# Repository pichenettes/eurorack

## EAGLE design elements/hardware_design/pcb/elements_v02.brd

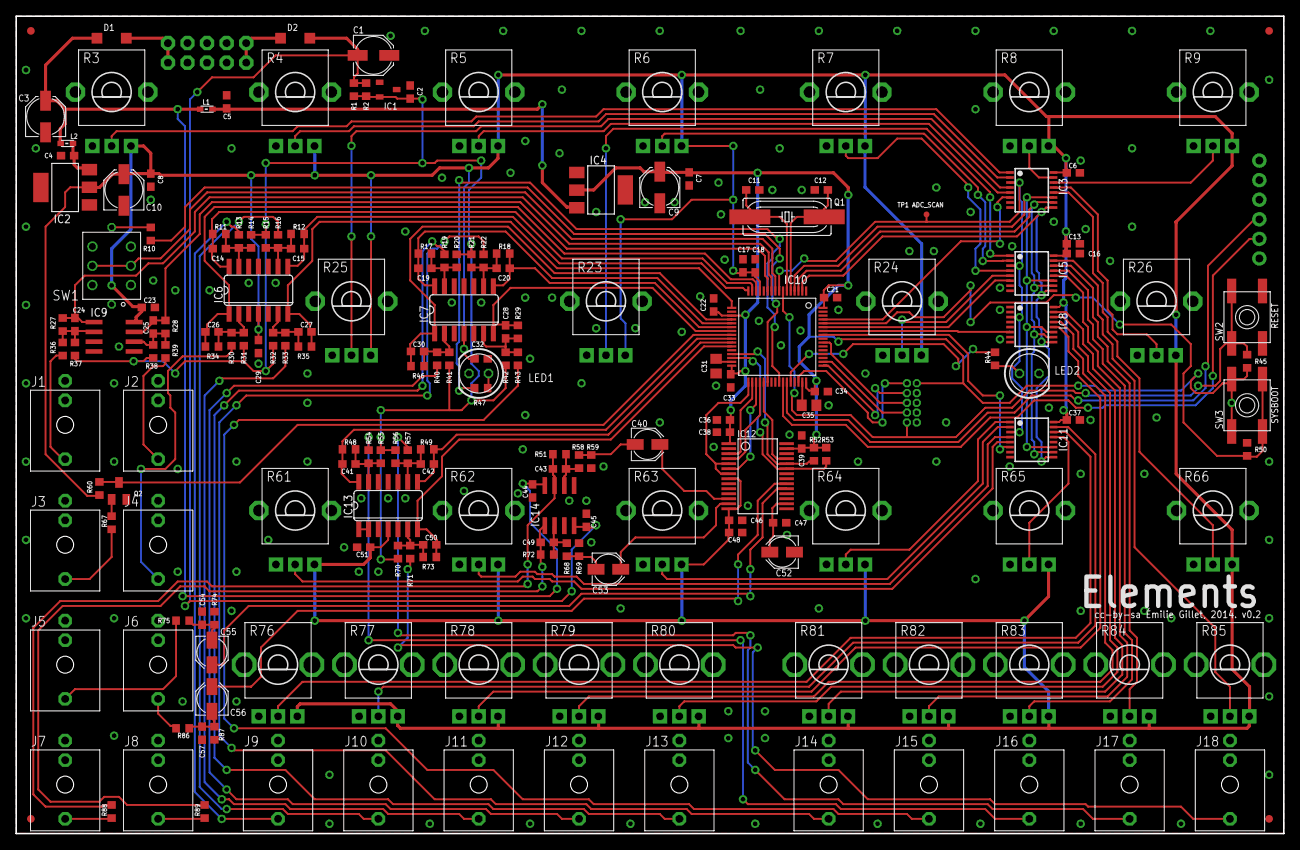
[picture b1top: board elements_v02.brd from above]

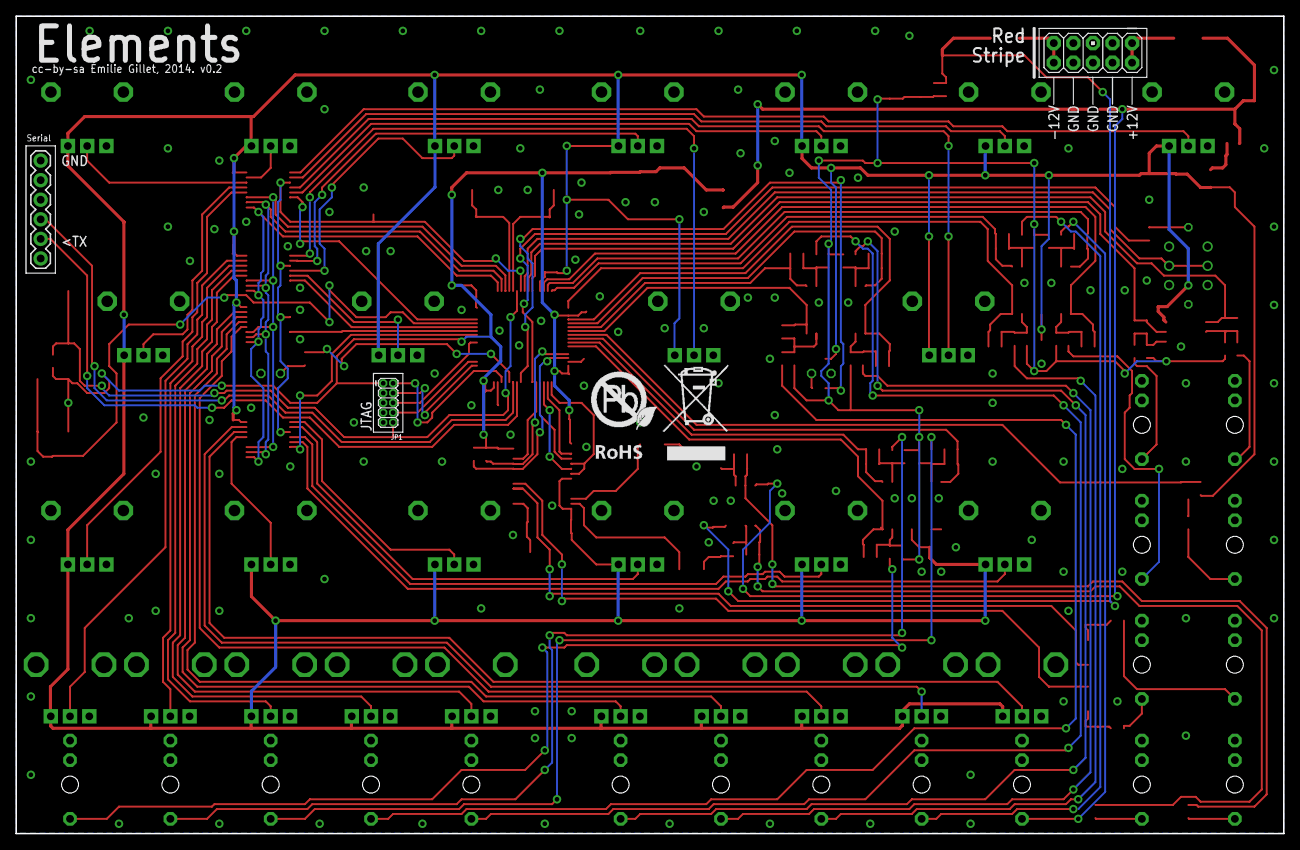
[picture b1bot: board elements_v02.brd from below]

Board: 2 copper layers, 164.5 x 106.0 mm, 198 parts (4 on the bottom side), 131 nets.

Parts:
C1, C3, C9, C10: 22u; PANASONIC_C
C2, C4, C5, C6, C7, C8, C13, C16, C18, C21, C22, C23, C29, C32, C33, C34, C37, C38, C39, C44, C45, C46, C47, C51: 100n; C0603
C11, C12, C43, C49: 18p; C0603
C14, C15, C19, C20, C24, C25, C26, C27, C28, C30, C41, C42, C50: 3.3n; C0603
C17, C36, C48: 1u; C0603
C31, C35: 2.2u; C0805
C40, C52, C53, C55, C56: 10u; PANASONIC_B
C54, C57: 220p; C0603
D1, D2: 1N5819HW; SOD123
F1, F2, F3, F4: FIDUCIAL1X2; FIDUCIAL-1X2
IC1: LM4040B10; DBZ_R-PDSO-G3
IC2, IC4: LM1117-3.3; SOT223
IC3, IC5, IC8, IC11: 4051PW; TSSOP16
IC6, IC7, IC13: MCP6004; SO14
IC9: MCP6002; SO08
IC10: STM32F405RGT6; TQFP-10X10-64
IC12: WM8731; SSOP28
IC14: LME49720; SO08
J1, J2, J3, J4, J5, J6, J7, J8, J9, J10, J11, J12, J13, J14, J15, J16, J17, J18: PJ301_THONKICONN6; WQP_PJ_301M6
JP1: M05X2MINIJTAG; 2X5-1.27
JP2: 1X06
JP3: M05X2PTH; AVR_ICSP
L1, L2: 0603
LED1: SSL-LX5093TC; LED5MM
LED2: SSL-LX5093PC; LED5MM
Q1: 8MHz; HC49UP
Q2: MMBT3904; SOT23-BEC
R1, R2, R88, R89: 1.0k; R0603
R3, R4, R5, R6, R7, R8, R9, R23, R24, R25, R26, R61, R62, R63, R64, R65, R66: 10kB; ALPS_POT_VERTICAL_PS
R10: 33; R0603
R11, R12, R17, R18, R28, R29, R35, R46, R48, R49, R73: 20k; R0603
R13, R16, R19, R22, R30, R33, R36, R39, R40, R43, R54, R57, R67, R71: 100k; R0603
R14, R15, R20, R21, R32, R38, R41, R42, R55, R56, R70: 120k; R0603
R27, R51, R59, R69, R72: 47k; R0603
R31: 200k; R0603
R34: 33k; R0603
R37: 180k; R0603
R44, R47, R52, R53: 2.2k; R0603
R45, R50, R60: 10k; R0603
R58, R68, R74, R87: 6.8k; R0603
R75, R86: 36k; R0603
R76, R77, R78, R79, R80, R81, R82, R83, R84, R85: 10kB; ALPS_POT_VERTICAL
SW1: LP4OA1PBCT
SW2, SW3: EVQ-Q2
TP1: ADC_TEST; PAD.03X.03
U$2: ROHS_BIG

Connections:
+3V3: C7.1, C9.+, C21.1, C22.1, C33.1, C34.1, C36.1, C38.1, C39.1, IC4.2, IC10.19, IC10.32, IC10.48, IC10.64, IC12.1, IC12.27, JP1.1, R45.2, R52.2, R53.2, SW3.B, SW3.B'
+3V3_A: C6.1, C8.1, C10.+, C13.1, C16.1, C17.1, C18.1, C23.1, C29.1, C32.1, C37.1, C46.1, C48.1, C51.1, IC2.2, IC3.16, IC5.16, IC6.4, IC7.4, IC8.16, IC9.8, IC10.13, IC11.16, IC12.8, IC12.14, IC13.4, R3.P$1, R4.P$1, R5.P$1, R6.P$1, R7.P$1, R8.P$1, R9.P$1, R23.P$1, R24.P$1, R25.P$1, R26.P$1, R60.2, R61.P$1, R62.P$1, R63.P$1, R64.P$1, R65.P$1, R66.P$1, R76.P$1, R77.P$1, R78.P$1, R79.P$1, R80.P$1, R81.P$1, R82.P$1, R83.P$1, R84.P$1, R85.P$1
ADC_ADDR_0: IC3.11, IC5.11, IC8.11, IC10.4, IC11.11
ADC_ADDR_1: IC3.10, IC5.10, IC8.10, IC10.3, IC11.10
ADC_ADDR_2: IC3.9, IC5.9, IC8.9, IC10.2, IC11.9
ADC_BANK_0: IC10.57, IC11.6
ADC_BANK_1: IC8.6, IC10.58
ADC_BANK_2: IC5.6, IC10.59
ADC_BANK_3: IC3.6, IC10.61
ADC_BLOW_SHAPE: C15.2, IC6.8, IC10.16, R12.1
ADC_BLOW_TIMBRE: C27.2, IC6.7, IC10.17, R35.1
ADC_BOW_TIMBRE: C14.2, IC6.14, IC10.15, R11.1
ADC_BRIGHTNESS: C42.2, IC10.26, IC13.8, R49.1
ADC_DAMPING: C20.2, IC7.8, IC10.22, R18.1
ADC_FM: C25.2, IC9.7, IC10.11, R28.1
ADC_GEOMETRY: C28.2, IC7.7, IC10.23, R29.1
ADC_POSITION: C41.2, IC10.25, IC13.14, R48.1
ADC_POTS: IC3.3, IC5.3, IC8.3, IC10.8, IC11.3, TP1.P$1
ADC_PRESSURE: C26.2, IC6.1, IC10.14, R34.1
ADC_SPACE: C50.2, IC10.27, IC13.7, R73.1
ADC_STRIKE_SHAPE: C30.2, IC7.1, IC10.20, R46.1
ADC_STRIKE_TIMBRE: C19.2, IC7.14, IC10.21, R17.1
ADC_V_OCT: C24.2, IC9.1, IC10.10, R27.1
AREF_-10: C2.1, IC1.2, R1.2, R2.2, R14.2, R15.2, R20.2, R21.2, R31.2, R32.2, R37.2, R38.2, R41.2, R42.2, R55.2, R56.2, R70.2
BOOT_FLASH: IC10.60, R50.2, SW3.A, SW3.A'
GATE: IC10.24, Q2.C, R60.1
GND: C1.+, C2.2, C3.-, C4.2, C5.2, C6.2, C7.2, C8.2, C9.-, C10.-, C11.1, C12.1, C13.2, C16.2, C17.2, C18.2, C21.2, C22.2, C23.2, C29.2, C31.2, C32.2, C33.2, C34.2, C35.2, C36.2, C37.2, C38.2, C39.2, C44.2, C45.1, C46.2, C47.2, C48.2, C51.2, C52.-, C54.2, C57.2, IC1.1, IC2.1, IC3.7, IC3.8, IC4.1, IC5.7, IC5.8, IC6.3, IC6.5, IC6.10, IC6.11, IC6.12, IC7.3, IC7.5, IC7.10, IC7.11, IC7.12, IC8.1, IC8.2, IC8.4, IC8.5, IC8.7, IC8.8, IC9.3, IC9.4, IC9.5, IC10.12, IC10.18, IC10.28, IC10.63, IC11.7, IC11.8, IC11.12, IC12.11, IC12.15, IC12.21, IC12.22, IC12.28, IC13.3, IC13.5, IC13.10, IC13.11, IC13.12, IC14.3, IC14.5, J1.P1, J2.P1, J3.P1, J3.P2, J4.P1, J5.P1, J6.P1, J7.P1, J8.P1, J9.P1, J10.P1, J11.P1, J12.P1, J13.P1, J14.P1, J15.P1, J16.P1, J17.P1, J18.P1, JP1.3, JP1.5, JP1.9, JP2.1, JP3.3, JP3.4, JP3.5, JP3.6, JP3.7, JP3.8, LED1.K, LED2.K, Q2.E, R3.P$3, R4.P$3, R5.P$3, R6.P$3, R7.P$3, R8.P$3, R9.P$3, R23.P$3, R24.P$3, R25.P$3, R26.P$3, R50.1, R59.1, R61.P$3, R62.P$3, R63.P$3, R64.P$3, R65.P$3, R66.P$3, R69.1, R74.1, R76.P$3, R77.P$3, R78.P$3, R79.P$3, R80.P$3, R81.P$3, R82.P$3, R83.P$3, R84.P$3, R85.P$3, R87.1, SW1.L2, SW1.P3, SW1.P6, SW2.A, SW2.A'
I2C_SCL: IC10.29, IC12.24, R52.1
I2C_SDA: IC10.30, IC12.23, R53.1
I2S_LRCK: IC10.33, IC12.5, IC12.7
I2S_MCK: IC10.37, IC12.25
I2S_SCK: IC10.34, IC12.3
I2S_SIN: IC10.35, IC12.6
I2S_SOUT: IC10.36, IC12.4
JTCK: IC10.49, JP1.4
JTDI: IC10.50, JP1.8
JTDO: IC10.55, JP1.6
JTMS: IC10.46, JP1.2
LED_GATE: IC10.38, R10.1
LIN: C56.+, IC12.20
LOUT: C40.+, IC12.12
LOUT_JACK: J8.P3, R89.1
unnamed: J10.P3, R16.2
unnamed: C15.1, IC6.9, R12.2, R15.1, R16.1
unnamed: J13.P3, R19.2
unnamed: J9.P3, R13.2
unnamed: C14.1, IC6.13, R11.2, R13.1, R14.1
unnamed: J2.P3, R39.2
unnamed: C12.2, IC10.5, Q1.2
unnamed: C11.2, IC10.6, Q1.1
unnamed: C19.1, IC7.13, R17.2, R19.1, R20.1
unnamed: J1.P3, R36.2
unnamed: C24.1, IC9.2, R27.2, R36.1, R37.1
unnamed: J14.P3, R22.2
unnamed: C35.1, IC10.47
unnamed: C20.1, IC7.9, R18.2, R21.1, R22.1
unnamed: C25.1, IC9.6, R28.2, R38.1, R39.1
unnamed: J12.P3, R40.2
unnamed: C47.1, C52.+, IC12.16
unnamed: C56.-, C57.1, R86.1, R87.2
unnamed: C31.1, IC10.31
unnamed: J5.P3, R75.2
unnamed: J6.P3, R86.2
unnamed: C54.1, C55.-, R74.2, R75.1
unnamed: C40.-, R58.2, R59.2
unnamed: C30.1, IC7.2, R40.1, R41.1, R46.2
unnamed: C43.1, IC14.6, R51.2, R58.1
unnamed: J11.P3, R33.2
unnamed: C27.1, IC6.6, R32.1, R33.1, R35.2
unnamed: C43.2, IC14.7, R51.1, R88.2
unnamed: J17.P3, R57.2
unnamed: C42.1, IC13.9, R49.2, R56.1, R57.1
unnamed: C53.-, R68.2, R69.2
unnamed: C49.1, IC14.2, R68.1, R72.2
unnamed: C49.2, IC14.1, R72.1, R89.2
unnamed: J18.P3, R71.2
unnamed: C50.1, IC13.6, R70.1, R71.1, R73.2
unnamed: J15.P3, R43.2
unnamed: C28.1, IC7.6, R29.2, R42.1, R43.1
unnamed: R10.2, SW1.L1
unnamed: J16.P3, R54.2
unnamed: C41.1, IC13.13, R48.2, R54.1, R55.1
unnamed: J4.P3, R30.2
unnamed: C26.1, IC6.2, R30.1, R31.1, R34.2
unnamed: J3.P3, R67.1
unnamed: IC13.1, IC13.2
unnamed: IC11.14, R76.P$2
unnamed: IC11.13, R65.P$2
unnamed: IC11.15, R77.P$2
unnamed: IC11.1, R64.P$2
unnamed: IC11.5, R61.P$2
unnamed: IC8.14, R80.P$2
unnamed: IC8.12, R78.P$2
unnamed: IC11.2, R63.P$2
unnamed: IC11.4, R62.P$2
unnamed: IC10.44, R44.1
unnamed: IC3.12, R66.P$2
unnamed: D1.A, JP3.1, JP3.2
unnamed: IC8.15, R81.P$2
unnamed: IC8.13, R79.P$2
unnamed: LED2.A, R44.2
unnamed: LED1.A, R47.2
unnamed: C5.1, IC4.3, L1.2
unnamed: IC3.13, R26.P$2
unnamed: IC3.15, R8.P$2
unnamed: D2.C, JP3.9, JP3.10
unnamed: IC5.12, R82.P$2
unnamed: Q2.B, R67.2
unnamed: IC5.4, R7.P$2
unnamed: IC3.14, R9.P$2
unnamed: IC5.2, R6.P$2
unnamed: IC5.5, R24.P$2
unnamed: IC5.1, R23.P$2
unnamed: IC3.4, R25.P$2
unnamed: IC3.2, R4.P$2
unnamed: IC3.1, R3.P$2
unnamed: IC3.5, R5.P$2
unnamed: IC5.13, R83.P$2
unnamed: IC5.14, R84.P$2
unnamed: IC5.15, R85.P$2
unnamed: IC10.41, R47.1
unnamed: C4.1, IC2.3, L2.2
RESET: IC10.7, JP1.10, R45.1, SW2.B, SW2.B'
RIN: C55.+, IC12.19
ROUT: C53.+, IC12.13
ROUT_JACK: J7.P3, R88.1
RX: IC10.43, JP2.4
SW_GATE: IC10.9, SW1.P2, SW1.P5
TX: IC10.42, JP2.5
VCC: C3.+, C44.1, D1.C, IC14.8, L1.1, L2.1
VEE: C1.-, C45.2, D2.A, IC14.4, R1.1, R2.1

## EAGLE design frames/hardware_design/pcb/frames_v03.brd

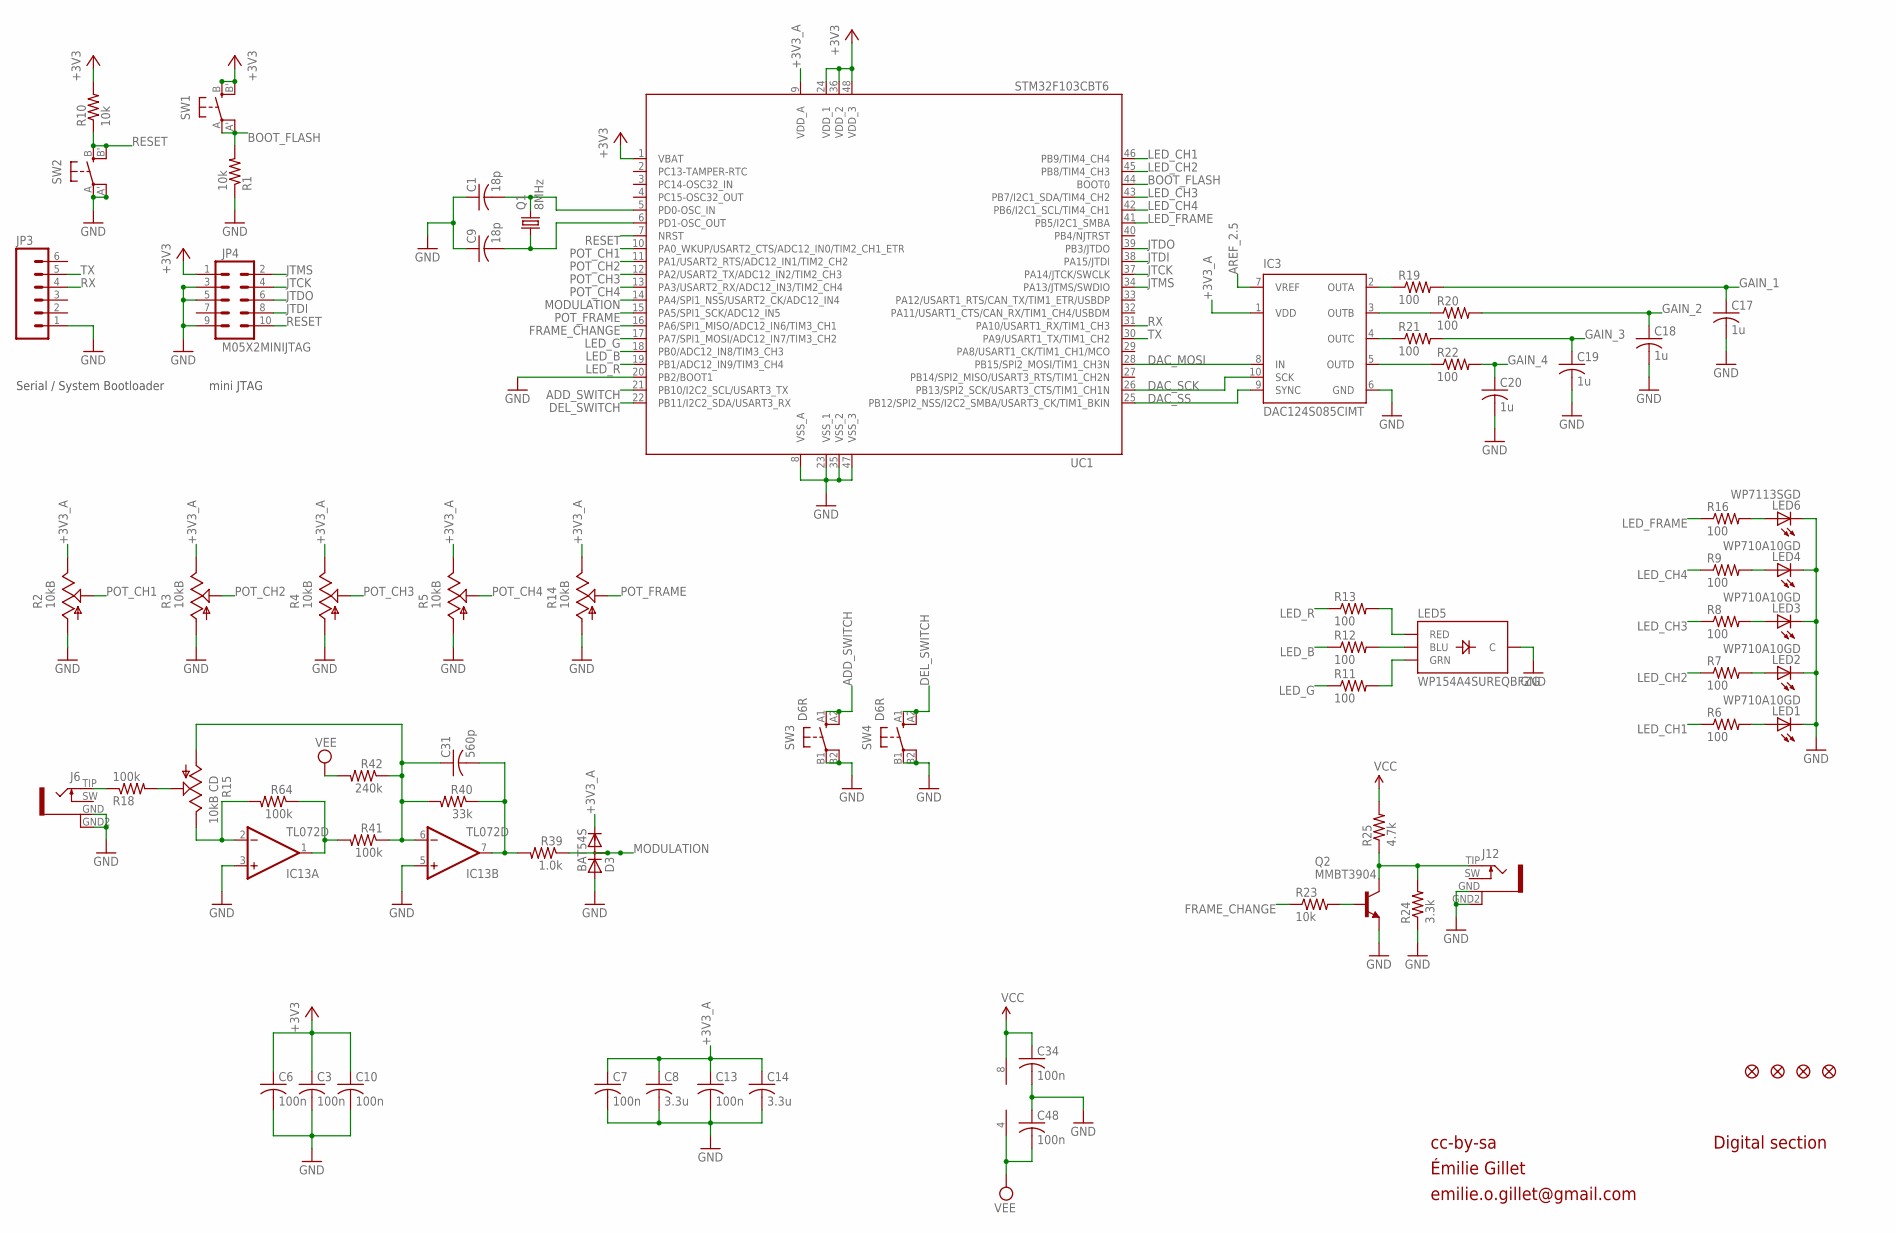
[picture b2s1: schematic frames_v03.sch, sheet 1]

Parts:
C1, C9: 18p; C0603
C3, C6, C7, C10, C13, C34, C48: 100n; C0603
C8, C14: 3.3u; C0603
C17, C18, C19, C20: 1u; C0603
C31: 560p; C0603
D3: BAT54S; SOT23
F1, F2, F3, F4: FIDUCIAL1X2; FIDUCIAL-1X2
IC3: DAC124S085CIMT; MSOP10
IC13: TL072D; SO08
J6, J12: PJ301WQP; WQP_PJ_301BM
JP3: M06SIP; 1X06
JP4: M05X2MINIJTAG; 2X5-1.27
LED1, LED2, LED3, LED4: WP710A10GD; LED3MM
LED5: WP154A4SUREQBFZG; LED-TRICOLOR-THROUGHHOLE
LED6: WP7113SGD; LED5MM
Q1: 8MHz; HC49UP
Q2: MMBT3904; SOT23-BEC
R1, R10, R23: 10k; R0603
R2, R3, R4, R5, R14: 10kB; ALPS_POT_VERTICAL_PS
R6, R7, R8, R9, R11, R12, R13, R16, R19, R20, R21, R22: 100; R0603
R15: 10kB CD; ALPS_POT_VERTICAL_PS
R18, R41, R64: 100k; R0603
R24: 3.3k; R0603
R25: 4.7k; R0603
R39: 1.0k; R0603
R40: 33k; R0603
R42: 240k; R0603
SW1, SW2: EVQQ2; EVQ-Q2
SW3, SW4: D6R
UC1: STM32F103CBT6; LQFP48

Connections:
+3V3: C3.1, C6.1, C10.1, JP4.1, R10.2, SW1.B (S), SW1.B' (S1), UC1.1 (VBAT), UC1.24 (VDD_1), UC1.36 (VDD_2), UC1.48 (VDD_3); also elsewhere on the board
+3V3_A: C7.1, C8.1, C13.1, C14.1, D3.2 (C), IC3.1 (VDD), R2.P$1 (E), R3.P$1 (E), R4.P$1 (E), R5.P$1 (E), R14.P$1 (E), UC1.9 (VDD_A); also elsewhere on the board
ADD_SWITCH: SW3.A1 (S), SW3.A2 (S1), UC1.21 (PB10/I2C2_SCL/USART3_TX)
AREF_2.5: IC3.7 (VREF); also elsewhere on the board
BOOT_FLASH: R1.2, SW1.A, SW1.A' (P1), UC1.44 (BOOT0)
DAC_MOSI: IC3.8 (IN), UC1.28 (PB15/SPI2_MOSI/TIM1_CH3N)
DAC_SCK: IC3.10 (SCK), UC1.26 (PB13/SPI2_SCK/USART3_CTS/TIM1_CH1N)
DAC_SS: IC3.9 (SYNC), UC1.25 (PB12/SPI2_NSS/I2C2_SMBA/USART3_CK/TIM1_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)
DEL_SWITCH: SW4.A1 (S), SW4.A2 (S1), UC1.22 (PB11/I2C2_SDA/USART3_RX)
FRAME_CHANGE: R23.1, UC1.16 (PA6/SPI1_MISO/ADC12_IN6/TIM3_CH1)
GAIN_1: C17.1, R19.2; also elsewhere on the board
GAIN_2: C18.1, R20.2; also elsewhere on the board
GAIN_3: C19.1, R21.2; also elsewhere on the board
GAIN_4: C20.1, R22.2; also elsewhere on the board
GATE2_LED: LED3.A, R8.2
GATE3_LED: LED2.A, R7.2
GATE4_LED: LED1.A, R6.2
GND: C1.1, C3.2, C6.2, C7.2, C8.2, C9.1, C10.2, C13.2, C14.2, C17.2, C18.2, C19.2, C20.2, C34.2, C48.1, D3.1 (A), IC3.6 (GND), IC13.3 (+IN), IC13.5 (+IN), J6.GND (1), J6.GND2 (4), J12.GND (1), J12.GND2 (4), JP3.1, JP4.3, JP4.5, JP4.9, LED1.K (C), LED2.K (C), LED3.K (C), LED4.K (C), LED5.GND (C), LED6.K (C), Q2.E, R1.1, R2.P$3 (A), R3.P$3 (A), R4.P$3 (A), R5.P$3 (A), R14.P$3 (A), R24.1, SW2.A, SW2.A' (P1), SW3.B1, SW3.B2 (P1), SW4.B1, SW4.B2 (P1), UC1.8 (VSS_A), UC1.20 (PB2/BOOT1), UC1.23 (VSS_1), UC1.35 (VSS_2), UC1.47 (VSS_3); also elsewhere on the board
JTCK: JP4.4, UC1.37 (PA14/JTCK/SWCLK)
JTDI: JP4.8, UC1.38 (PA15/JTDI)
JTDO: JP4.6, UC1.39 (PB3/JTDO)
JTMS: JP4.2, UC1.34 (PA13/JTMS/SWDIO)
LED_B: R12.1, UC1.18 (PB0/ADC12_IN8/TIM3_CH3)
LED_CH1: R6.1, UC1.46 (PB9/TIM4_CH4)
LED_CH2: R7.1, UC1.45 (PB8/TIM4_CH3)
LED_CH3: R8.1, UC1.43 (PB7/I2C1_SDA/TIM4_CH2)
LED_CH4: R9.1, UC1.42 (PB6/I2C1_SCL/TIM4_CH1)
LED_FRAME: R16.1, UC1.41 (PB5/I2C1_SMBA)
LED_G: R11.1, UC1.17 (PA7/SPI1_MOSI/ADC12_IN7/TIM3_CH2)
LED_R: R13.1, UC1.19 (PB1/ADC12_IN9/TIM3_CH4)
MODULATION: D3.3 (AC), R39.1, UC1.14 (PA4/SPI1_NSS/USART2_CK/ADC12_IN4)
unnamed: IC13.2 (-IN), R15.P$1 (E), R64.2
unnamed: R15.P$2 (S), R18.2
unnamed: LED4.A, R9.2
unnamed: C1.2, Q1.2, UC1.5 (PD0-OSC_IN)
unnamed: C9.2, Q1.1, UC1.6 (PD1-OSC_OUT)
unnamed: IC13.1 (OUT), R41.2, R64.1
unnamed: J6.TIP (2), R18.1
unnamed: C31.2, IC13.7 (OUT), R39.2, R40.1
unnamed: C31.1, IC13.6 (-IN), R15.P$3 (A), R40.2, R41.1, R42.1
unnamed: LED6.A, R16.2
unnamed: LED5.RED, R13.2
unnamed: LED5.BLU, R12.2
unnamed: LED5.GRN, R11.2
unnamed: IC3.2 (OUTA), R19.1
unnamed: IC3.3 (OUTB), R20.1
unnamed: IC3.4 (OUTC), R21.1
unnamed: J12.TIP (2), Q2.C, R24.2, R25.1
unnamed: IC3.5 (OUTD), R22.1
unnamed: Q2.B, R23.2
POT_CH1: R2.P$2 (S), UC1.10 (PA0_WKUP/USART2_CTS/ADC12_IN0/TIM2_CH1_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)
POT_CH2: R3.P$2 (S), UC1.11 (PA1/USART2_RTS/ADC12_IN1/TIM2_CH2)
POT_CH3: R4.P$2 (S), UC1.12 (PA2/USART2_TX/ADC12_IN2/TIM2_CH3)
POT_CH4: R5.P$2 (S), UC1.13 (PA3/USART2_RX/ADC12_IN3/TIM2_CH4)
POT_FRAME: R14.P$2 (S), UC1.15 (PA5/SPI1_SCK/ADC12_IN5)
RESET: JP4.10, R10.1, SW2.B (S), SW2.B' (S1), UC1.7 (NRST)
RX: JP3.4, UC1.31 (PA10/USART1_RX/TIM1_CH3)
TX: JP3.5, UC1.30 (PA9/USART1_TX/TIM1_CH2)
VCC: C34.1, IC13.8 (V+), R25.2; also elsewhere on the board
VEE: C48.2, IC13.4 (V-), R42.2; also elsewhere on the board

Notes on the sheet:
cc-by-sa
Serial / System Bootloader
mini JTAG
Digital section
Émilie Gillet
emilie.o.gillet@gmail.com

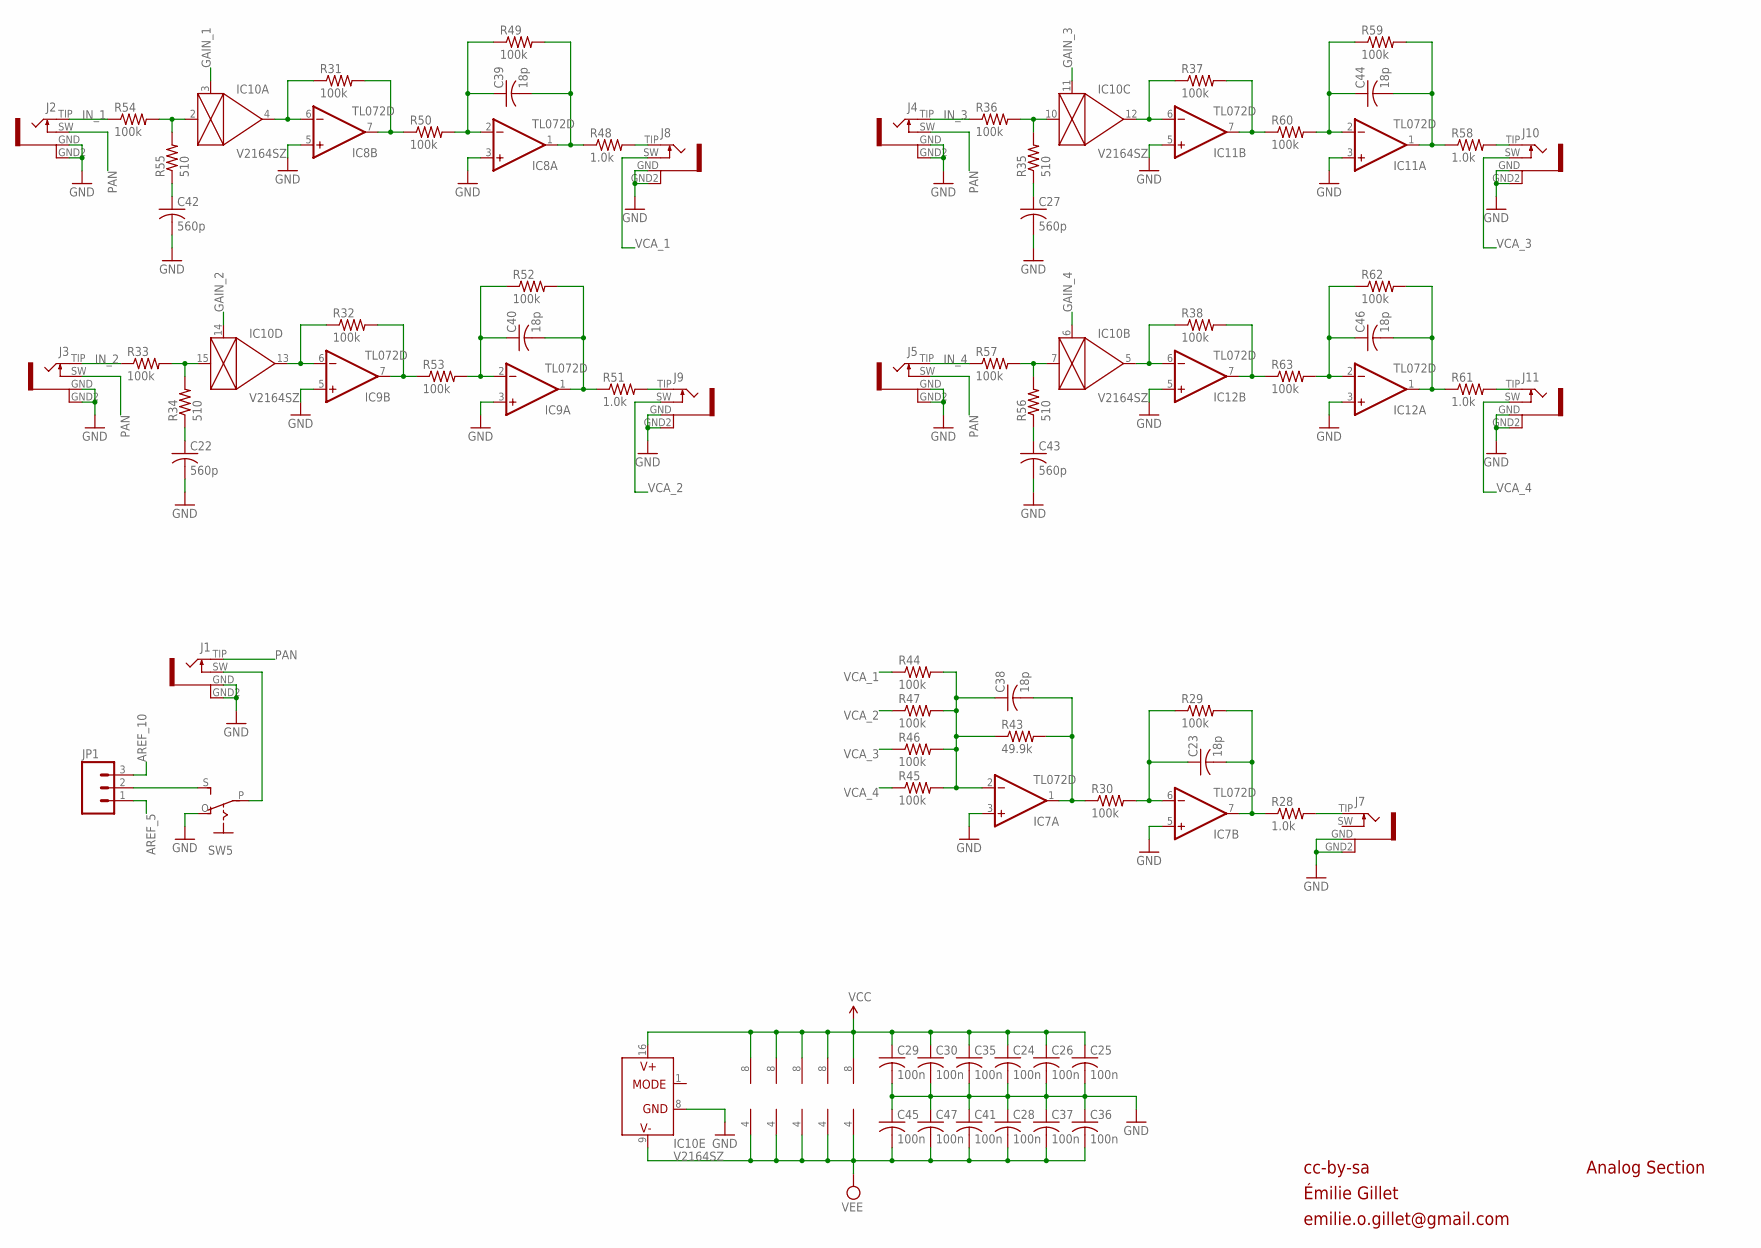
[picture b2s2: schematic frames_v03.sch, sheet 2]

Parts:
C22, C27, C42, C43: 560p; C0603
C23, C38, C39, C40, C44, C46: 18p; C0603
C24, C25, C26, C28, C29, C30, C35, C36, C37, C41, C45, C47: 100n; C0603
IC7, IC8, IC9, IC11, IC12: TL072D; SO08
IC10: V2164SZ; SOIC16N
J1, J2, J3, J4, J5, J7, J8, J9, J10, J11: PJ301WQP; WQP_PJ_301BM
JP1: M03PTH; 1X03
R28, R48, R51, R58, R61: 1.0k; R0603
R29, R30, R31, R32, R33, R36, R37, R38, R44, R45, R46, R47, R49, R50, R52, R53, R54, R57, R59, R60, R62, R63: 100k; R0603
R34, R35, R55, R56: 510; R0603
R43: 49.9k; R0603
SW5: S-ON-ONSMALL_SLIDE; ES_100SP1T6B11M2QEH_SMALL

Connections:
AREF_5: JP1.1; also elsewhere on the board
AREF_10: JP1.3; also elsewhere on the board
FB_CURRENT: IC10.2 (IN), R54.2, R55.2
FB_CURRENT1: IC10.15 (IN), R33.2, R34.2
FB_CURRENT2: IC10.10 (IN), R35.2, R36.2
FB_CURRENT3: IC10.7 (IN), R56.2, R57.2
GAIN_1: IC10.3 (CTRL); also elsewhere on the board
GAIN_2: IC10.14 (CTRL); also elsewhere on the board
GAIN_3: IC10.11 (CTRL); also elsewhere on the board
GAIN_4: IC10.6 (CTRL); also elsewhere on the board
GND: C22.2, C24.2, C25.2, C26.2, C27.2, C28.1, C29.2, C30.2, C35.2, C36.1, C37.1, C41.1, C42.2, C43.2, C45.1, C47.1, IC7.3 (+IN), IC7.5 (+IN), IC8.3 (+IN), IC8.5 (+IN), IC9.3 (+IN), IC9.5 (+IN), IC10.8 (GND), IC11.3 (+IN), IC11.5 (+IN), IC12.3 (+IN), IC12.5 (+IN), J1.GND (1), J1.GND2 (4), J2.GND (1), J2.GND2 (4), J3.GND (1), J3.GND2 (4), J4.GND (1), J4.GND2 (4), J5.GND (1), J5.GND2 (4), J7.GND (1), J7.GND2 (4), J8.GND (1), J8.GND2 (4), J9.GND (1), J9.GND2 (4), J10.GND (1), J10.GND2 (4), J11.GND (1), J11.GND2 (4), SW5.O; also elsewhere on the board
IN_1: J2.TIP (2), R54.1
IN_2: J3.TIP (2), R33.1
IN_3: J4.TIP (2), R36.1
IN_4: J5.TIP (2), R57.1
unnamed: C42.1, R55.1
unnamed: J7.TIP (2), R28.2
unnamed: IC9.7 (OUT), R32.2, R53.1
unnamed: C27.1, R35.1
unnamed: IC8.6 (-IN), IC10.4 (OUT), R31.1
unnamed: C39.1, IC8.2 (-IN), R49.1, R50.2
unnamed: C39.2, IC8.1 (OUT), R48.1, R49.2
unnamed: C23.2, IC7.7 (OUT), R28.1, R29.2
unnamed: C22.1, R34.1
unnamed: C38.1, IC7.2 (-IN), R43.1, R44.2, R45.2, R46.2, R47.2
unnamed: IC9.6 (-IN), IC10.13 (OUT), R32.1
unnamed: C23.1, IC7.6 (-IN), R29.1, R30.2
unnamed: C40.1, IC9.2 (-IN), R52.1, R53.2
unnamed: C40.2, IC9.1 (OUT), R51.1, R52.2
unnamed: IC10.12 (OUT), IC11.6 (-IN), R37.1
unnamed: C44.1, IC11.2 (-IN), R59.1, R60.2
unnamed: C44.2, IC11.1 (OUT), R58.1, R59.2
unnamed: C43.1, R56.1
unnamed: C38.2, IC7.1 (OUT), R30.1, R43.2
unnamed: IC10.5 (OUT), IC12.6 (-IN), R38.1
unnamed: C46.1, IC12.2 (-IN), R62.1, R63.2
unnamed: C46.2, IC12.1 (OUT), R61.1, R62.2
unnamed: J1.SW (3), SW5.P
unnamed: J8.TIP (2), R48.2
unnamed: JP1.2, SW5.S
unnamed: IC12.7 (OUT), R38.2, R63.1
unnamed: J9.TIP (2), R51.2
unnamed: J11.TIP (2), R61.2
unnamed: J10.TIP (2), R58.2
PAN: J1.TIP (2), J2.SW (3), J3.SW (3), J4.SW (3), J5.SW (3)
VCA0_1: IC8.7 (OUT), R31.2, R50.1
VCA0_3: IC11.7 (OUT), R37.2, R60.1
VCA_1: J8.SW (3), R44.1
VCA_2: J9.SW (3), R47.1
VCA_3: J10.SW (3), R46.1
VCA_4: J11.SW (3), R45.1
VCC: C24.1, C25.1, C26.1, C29.1, C30.1, C35.1, IC7.8 (V+), IC8.8 (V+), IC9.8 (V+), IC10.16 (V+), IC11.8 (V+), IC12.8 (V+); also elsewhere on the board
VEE: C28.2, C36.2, C37.2, C41.2, C45.2, C47.2, IC7.4 (V-), IC8.4 (V-), IC9.4 (V-), IC10.9 (V-), IC11.4 (V-), IC12.4 (V-); also elsewhere on the board

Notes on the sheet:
cc-by-sa
Analog Section
Émilie Gillet
emilie.o.gillet@gmail.com

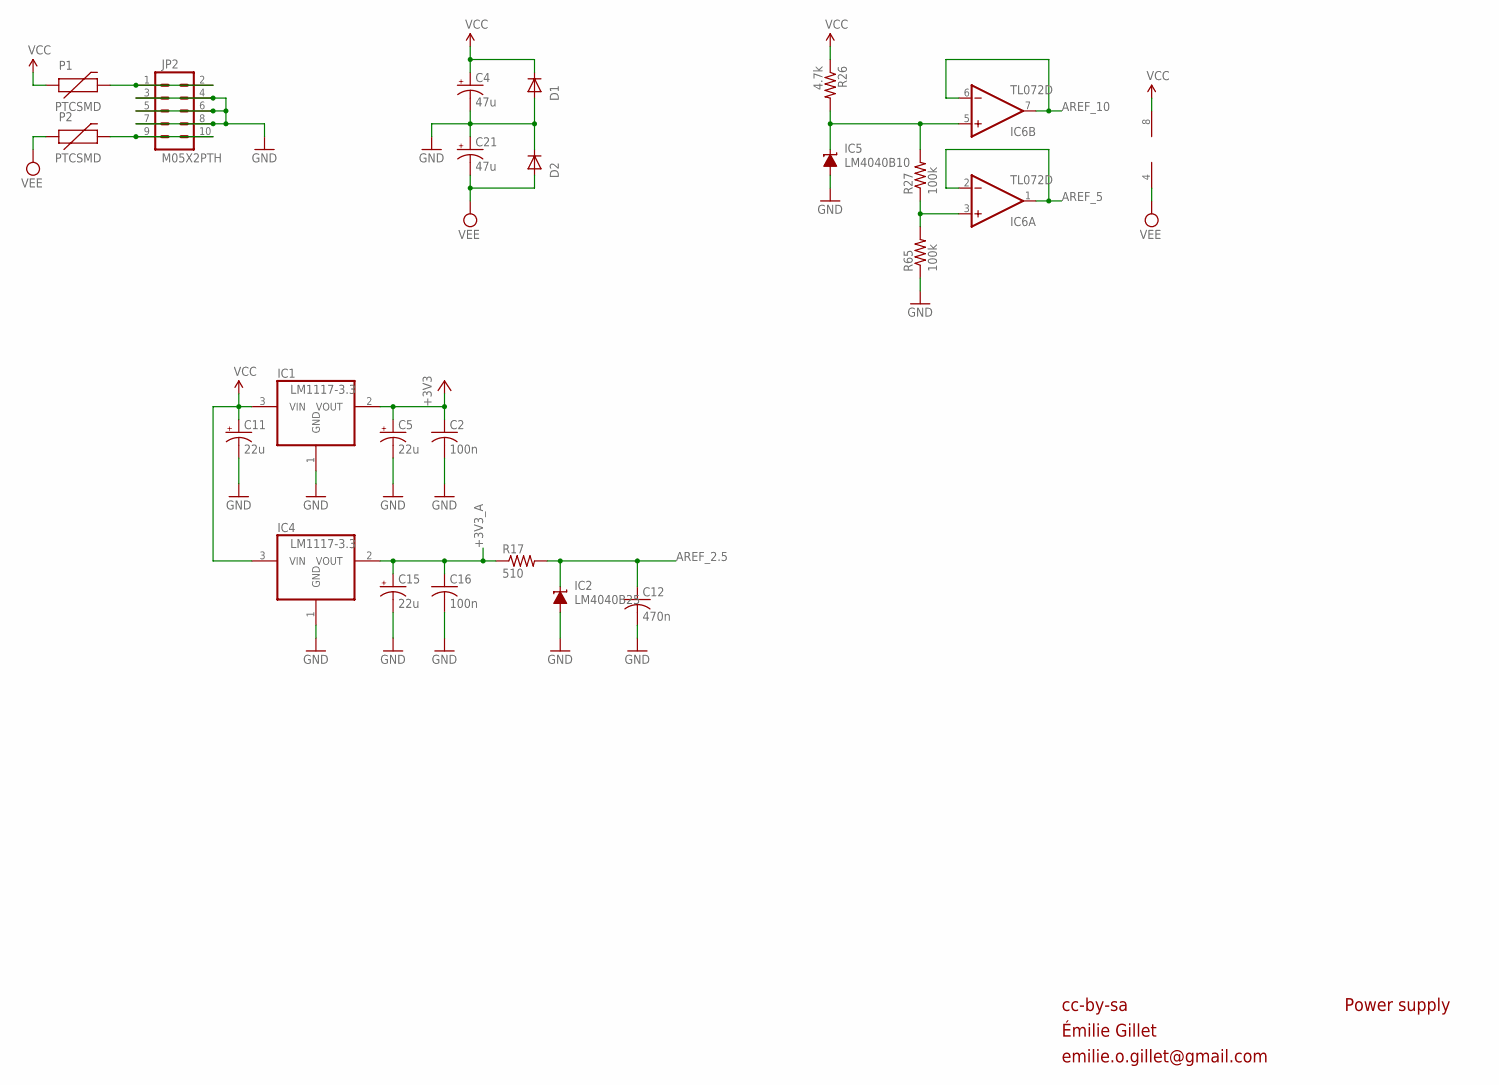
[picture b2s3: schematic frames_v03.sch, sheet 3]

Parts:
C2, C16: 100n; C0603
C4, C21: 47u; PANASONIC_D
C5, C11, C15: 22u; PANASONIC_C
C12: 470n; C0603
D1, D2: 1N5819HW; SOD123
IC1, IC4: LM1117-3.3; SOT223
IC2: LM4040B25; DBZ_R-PDSO-G3
IC5: LM4040B10; DBZ_R-PDSO-G3
IC6: TL072D; SO08
JP2: M05X2PTH; AVR_ICSP
P1, P2: PTCSMD; PTC-1206
R17: 510; R0603
R26: 4.7k; R0603
R27, R65: 100k; R0603

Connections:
+3V3: C2.1, C5.+, IC1.2 (VOUT); also elsewhere on the board
+3V3_A: C15.+, C16.1, IC4.2 (VOUT), R17.1; also elsewhere on the board
AREF_2.5: C12.1, IC2.1 (C), R17.2; also elsewhere on the board
AREF_5: IC6.1 (OUT), IC6.2 (-IN); also elsewhere on the board
AREF_10: IC6.6 (-IN), IC6.7 (OUT); also elsewhere on the board
AREF_10_0: IC5.1 (C), IC6.5 (+IN), R26.2, R27.2
GND: C2.2, C4.-, C5.-, C11.-, C12.2, C15.-, C16.2, C21.+, D1.A, D2.C, IC1.1 (GND), IC2.2 (A), IC4.1 (GND), IC5.2 (A), JP2.3, JP2.4, JP2.5, JP2.6, JP2.7, JP2.8, R65.1; also elsewhere on the board
unnamed: IC6.3 (+IN), R27.1, R65.2
unnamed: JP2.1, JP2.2, P1.2
unnamed: JP2.9, JP2.10, P2.2
VCC: C4.+, C11.+, D1.C, IC1.3 (VIN), IC4.3 (VIN), IC6.8 (V+), P1.1, R26.1; also elsewhere on the board
VEE: C21.-, D2.A, IC6.4 (V-), P2.1; also elsewhere on the board

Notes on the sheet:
cc-by-sa
Power supply
Émilie Gillet
emilie.o.gillet@gmail.com

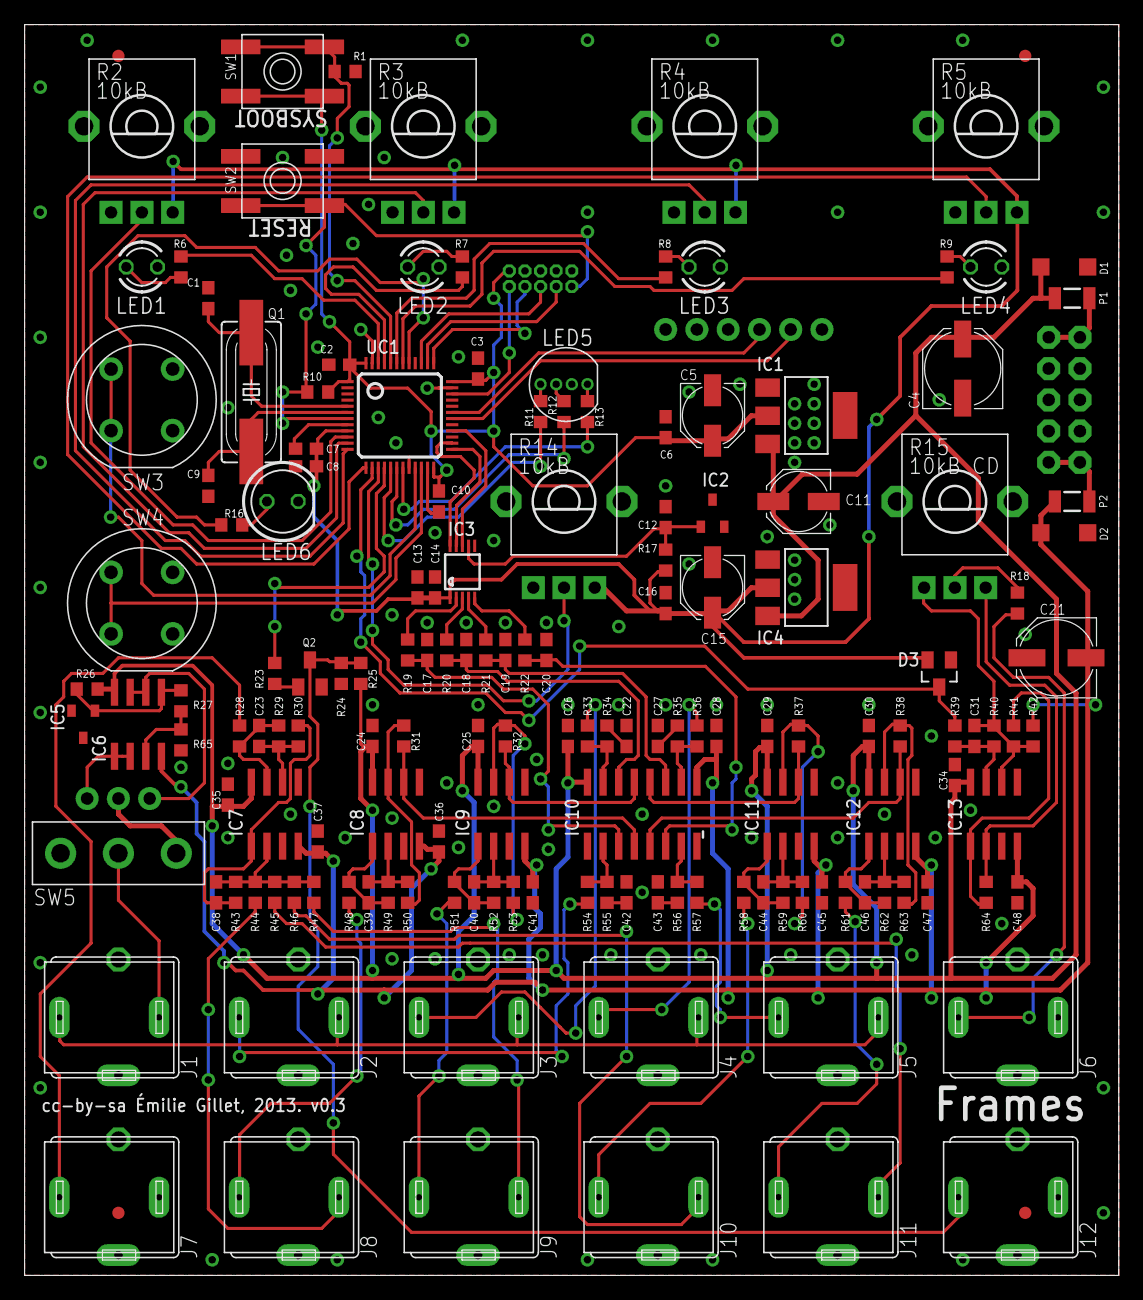
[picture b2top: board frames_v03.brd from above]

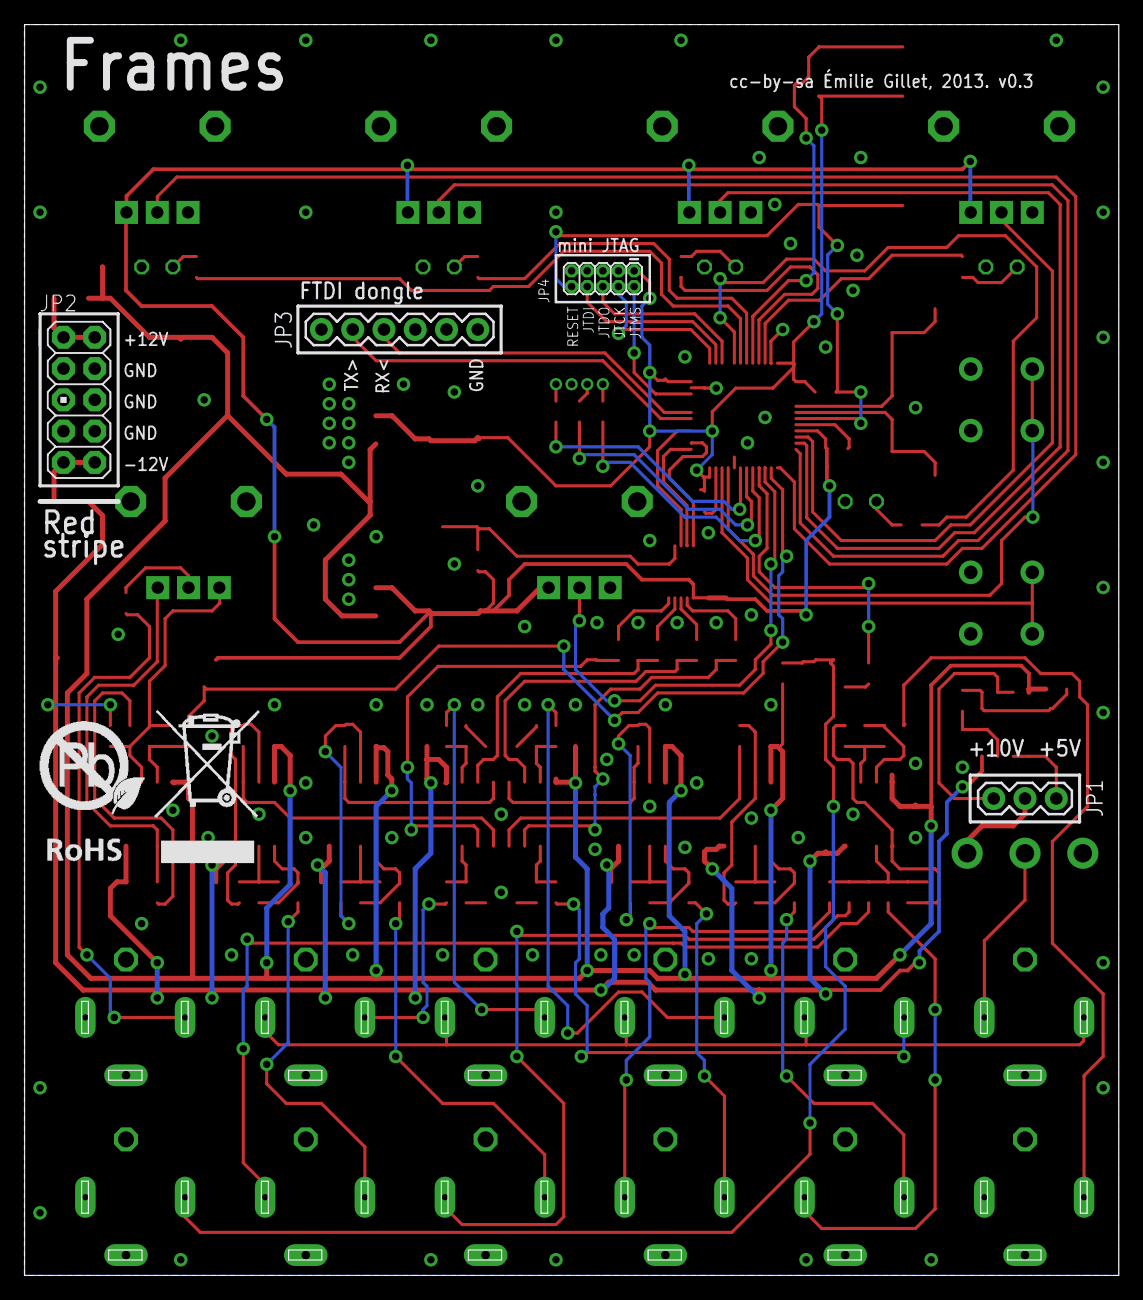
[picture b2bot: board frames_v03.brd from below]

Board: 2 copper layers, 88.9 x 101.6 mm, 165 parts (5 on the bottom side), 110 nets.

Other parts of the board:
U$1: EURORACK_TEMPLATE
U$3: ROHS_BIG

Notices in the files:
grids/hardware_design/pcb/grids_v02.brd:
cc-by-sa Émilie Gillet
kinks/hardware_design/pcb/kinks_v41.brd:
cc-by-sa Émilie Gillet, 2015. v4
